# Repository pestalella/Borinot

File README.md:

# Borinot
Sensor de temperatura i humitat, que envia les dades que recull a una base de dades via WiFi

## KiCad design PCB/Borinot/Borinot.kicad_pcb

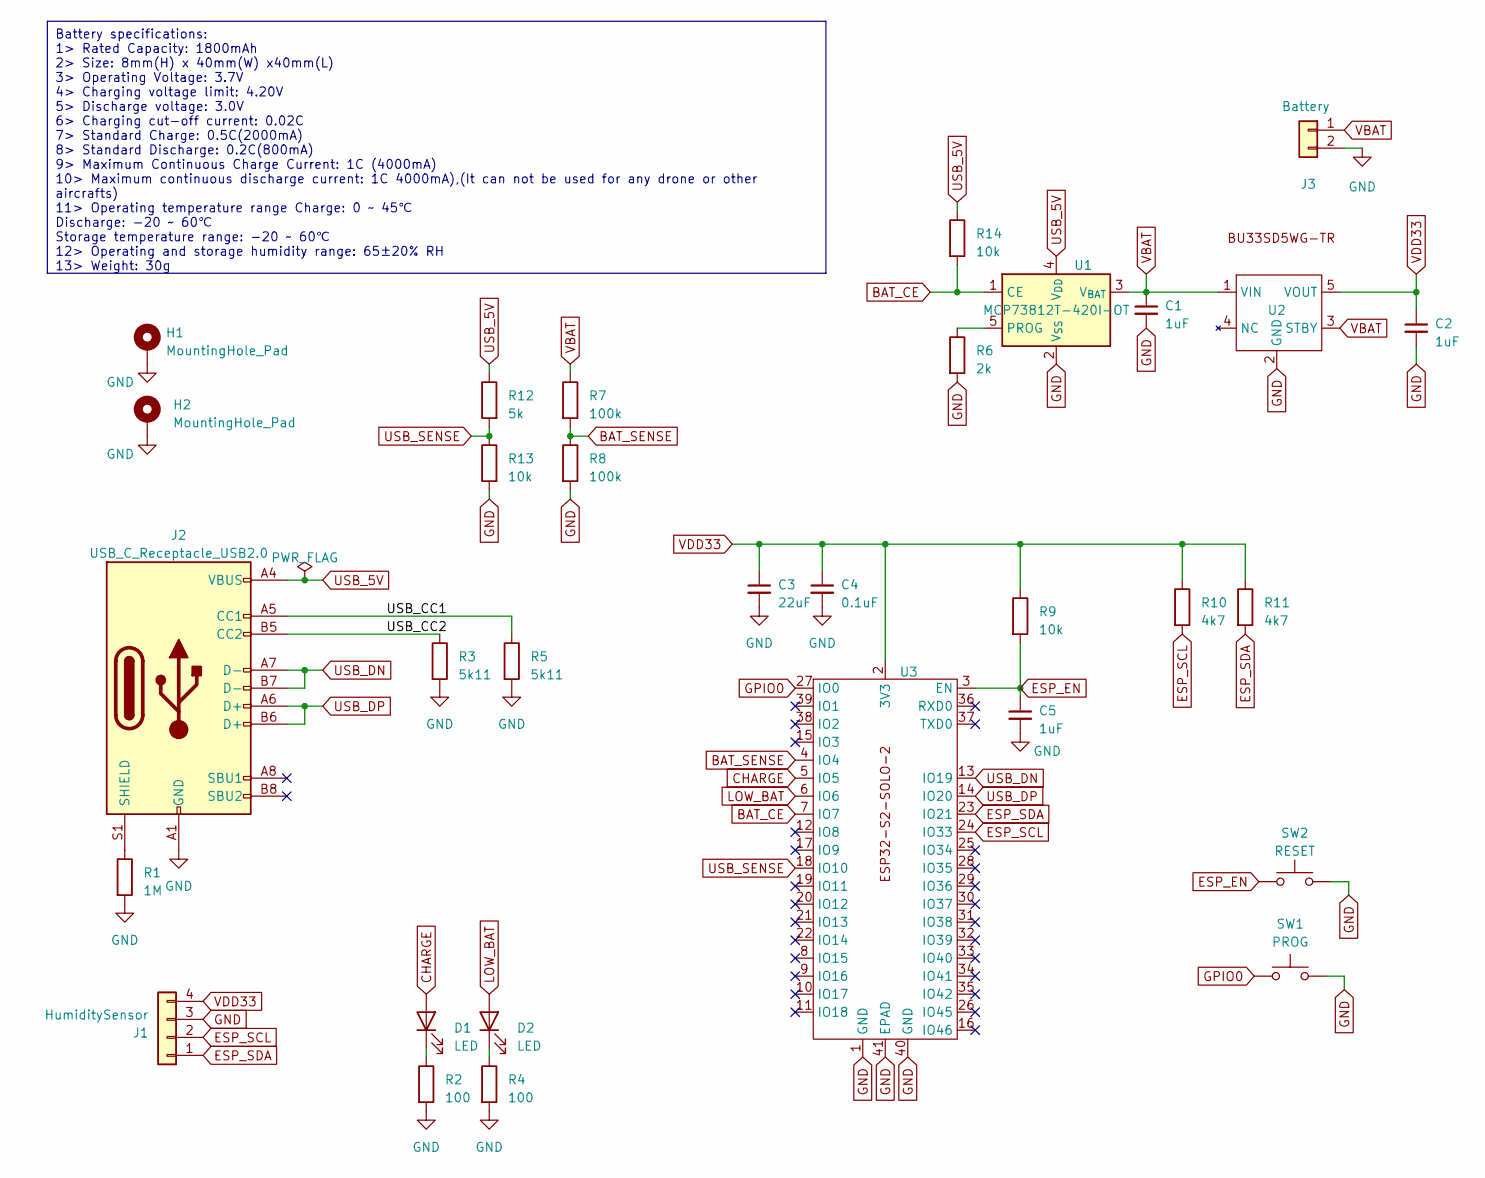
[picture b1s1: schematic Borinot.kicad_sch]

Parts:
C1, C2, C5: 1uF; C_0805_2012Metric_Pad1.18x1.45mm_HandSolder
C3: 22uF; C_0805_2012Metric_Pad1.18x1.45mm_HandSolder
C4: 0.1uF; C_0805_2012Metric_Pad1.18x1.45mm_HandSolder
D1, D2: LED; LED_0805_2012Metric
H1, H2: MountingHole_Pad; MountingHole_3.2mm_M3_Pad_Via
J1: HumiditySensor; Molex_KK-254_AE-6410-04A_1x04_P2.54mm_Vertical
J2: USB_C_Receptacle_USB2.0; USB_C_Receptacle_G-Switch_GT-USB-7010ASV
J3: Battery; PinHeader_1x02_P2.54mm_Vertical
R1: 1M; R_0805_2012Metric_Pad1.20x1.40mm_HandSolder
R2, R4: 100; R_0805_2012Metric_Pad1.20x1.40mm_HandSolder
R3, R5: 5k11; R_0805_2012Metric_Pad1.20x1.40mm_HandSolder
R6: 2k; R_0805_2012Metric_Pad1.20x1.40mm_HandSolder
R7, R8: 100k; R_0805_2012Metric_Pad1.20x1.40mm_HandSolder
R9, R13, R14: 10k; R_0805_2012Metric_Pad1.20x1.40mm_HandSolder
R10, R11: 4k7; R_0805_2012Metric_Pad1.20x1.40mm_HandSolder
R12: 5k; R_0805_2012Metric_Pad1.20x1.40mm_HandSolder
SW1: PROG; SW_PUSH_6mm
SW2: RESET; SW_PUSH_6mm
U1: MCP73812T-420I-OT; SOT-23-5
U2: SOT-23-5
U3: ESP32-S2-SOLO

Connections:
/USB_CC1: J2.A5 (CC1), R5.1
/USB_CC2: J2.B5 (CC2), R3.1
BAT_CE: R14.2, U1.1 (CE), U3.7 (IO7)
BAT_SENSE: R7.2, R8.1, U3.4 (IO4)
CHARGE: D1.2 (A), U3.5 (IO5)
ESP_EN: C5.1, R9.2, SW2.1, U3.3 (EN)
ESP_SCL: J1.2, R10.2, U3.24 (IO33)
ESP_SDA: J1.1, R11.2, U3.23 (IO21)
GND: C1.2, C2.2, C3.2, C4.2, C5.2, H1.1, H2.1, J1.3, J2.A1 (GND), J2.A12 (GND), J2.B1 (GND), J2.B12 (GND), J3.2, R1.2, R2.2, R3.2, R4.2, R5.2, R6.2, R8.2, R13.2, SW1.2, SW2.2, U1.2 (V_{SS}), U2.2 (GND), U3.1 (GND), U3.40 (GND), U3.41 (EPAD)
GPIO0: SW1.1, U3.27 (IO0)
LOW_BAT: D2.2 (A), U3.6 (IO6)
unnamed: D1.1 (K), R2.1
unnamed: D2.1 (K), R4.1
unnamed: J2.S1 (SHIELD), R1.1
unnamed: R6.1, U1.5 (PROG)
USB_5V: J2.A4 (VBUS), J2.A9 (VBUS), J2.B4 (VBUS), J2.B9 (VBUS), R12.1, R14.1, U1.4 (V_{DD})
USB_DN: J2.A7 (D-), J2.B7 (D-), U3.13 (IO19)
USB_DP: J2.A6 (D+), J2.B6 (D+), U3.14 (IO20)
USB_SENSE: R12.2, R13.1, U3.18 (IO10)
VBAT: C1.1, J3.1, R7.1, U1.3 (V_{BAT}), U2.1 (VIN), U2.3 (STBY)
VDD33: C2.1, C3.1, C4.1, J1.4, R9.1, R10.1, R11.1, U2.5 (VOUT), U3.2 (3V3)

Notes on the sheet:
Battery specifications: 1> Rated Capacity: 1800mAh 2> Size: 8mm(H) x 40mm(W) x40mm(L) 3> Operating Voltage: 3.7V 4> Charging voltage limit: 4.20V 5> Discharge voltage: 3.0V 6> Charging cut-off current: 0.02C 7> Standard Charge: 0.5C(2000mA) 8> Standard Discharge: 0.2C(800mA) 9> Maximum Continuous C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

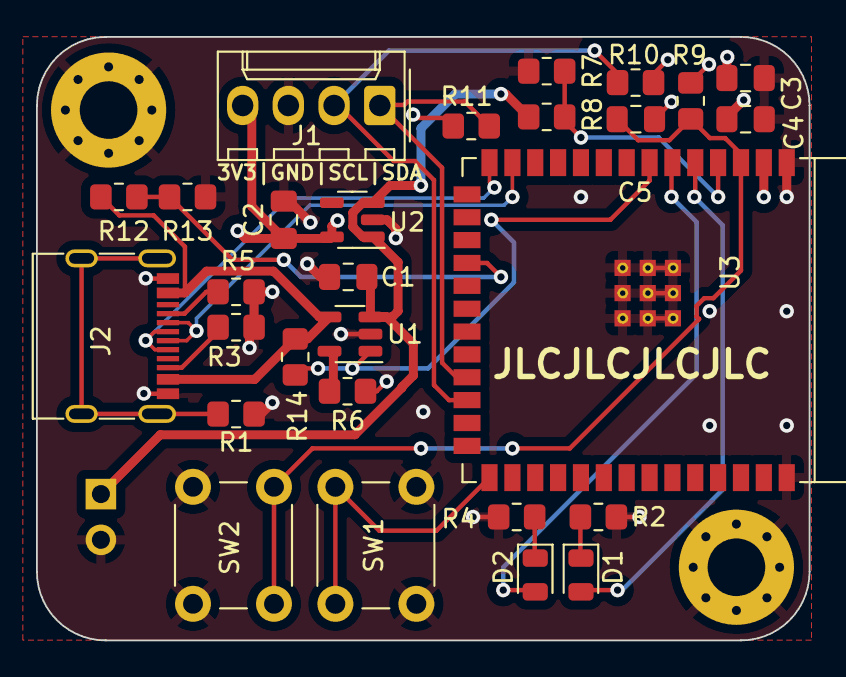
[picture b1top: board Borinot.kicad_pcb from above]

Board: 4 copper layers, 42.9 x 33.5 mm, 31 parts (1 on the bottom side), 21 nets.

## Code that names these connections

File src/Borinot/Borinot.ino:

#include "passwords.h"

#include "Adafruit_Sensor.h"
#include "Adafruit_AM2320.h"
#include "driver/adc.h"
#include "esp_adc_cal.h"
#include "esp_mac.h"
#include <Wire.h>

#include <WiFiMulti.h>
WiFiMulti wifiMulti;
#define DEVICE "ESP32"
#include <InfluxDbClient.h>
#include <InfluxDbCloud.h>

const char *ssid = WIFI_SSID;
const char *password = WIFI_PASSWORD;

// Time zone info
#define TZ_INFO "UTC2"

TwoWire I2CAM2320 = TwoWire(0);
Adafruit_AM2320 am2320 = Adafruit_AM2320(&I2CAM2320);

const int CHARGING_PIN = GPIO_NUM_5;
const int LOW_BAT_PIN = GPIO_NUM_6;
const int USB_SENSE = GPIO_NUM_10;

const int BAT_CHARGE_ENABLE = GPIO_NUM_7;

const int BATTERY_VOLTAGE_START_CHARGE = 3500;
const int BATTERY_VOLTAGE_STOP_CHARGE = 4150;

int batteryPoweredDelay = 10000; // 10 second delay
int millisecondsBetweenPosts = 600000;
int accumDelayBeforeSending = 0;

// Declare InfluxDB client instance with preconfigured InfluxCloud certificate
InfluxDBClient client(INFLUXDB_URL, INFLUXDB_ORG, INFLUXDB_BUCKET, INFLUXDB_TOKEN, InfluxDbCloud2CACert);

// Declare Data point
Point sensor("air_quality");

String h2S(uint8_t num)
{
	return (num < 16 ? "0" : "") + String(num, HEX);
}

void setup()
{
	Serial.begin(115200);
	pinMode(CHARGING_PIN, OUTPUT); // Indicator LED
	pinMode(LOW_BAT_PIN, OUTPUT);	 // Indicator LED
	pinMode(CHARGING_PIN, OUTPUT); // Indicator LED

	pinMode(USB_SENSE, INPUT_PULLDOWN); // USB sense pin (connected to USB 5V)
	pinMode(BAT_CHARGE_ENABLE, OUTPUT); // Battery charge enable pin

	delay(10);
	digitalWrite(BAT_CHARGE_ENABLE, 0); // Disable charging when starting

	if (!I2CAM2320.begin(21, 33))
	{
		Serial.println("Couldn't initialize I2C");
	}
	else
	{
		// unsigned status = bme.begin(0x77, &I2CAM2320);
		bool status = am2320.begin();

		if (!status)
		{
			Serial.println("Could not find a valid AM320 sensor, check wiring");
		}
	}

	// Setup wifi
	WiFi.mode(WIFI_STA);
	wifiMulti.addAP(ssid, password);

	Serial.print("Connecting to wifi");
	while (wifiMulti.run() != WL_CONNECTED)
	{
		Serial.print(".");
		delay(100);
	}
	Serial.println();

	// Accurate time is necessary for certificate validation and writing in batches
	// We use the NTP servers in your area as provided by: https://www.pool.ntp.org/zone/
	// Syncing progress and the time will be printed to Serial.
	timeSync(TZ_INFO, "pool.ntp.org", "time.nis.gov");

	// Check server connection
	if (client.validateConnection())
	{
		Serial.print("Connected to InfluxDB: ");
		Serial.println(client.getServerUrl());
	}
	else
	{
		Serial.print("InfluxDB connection failed: ");
		Serial.println(client.getLastErrorMessage());
	}

	uint8_t macAddress[10];
	if (esp_efuse_mac_get_default(macAddress) == ESP_OK)
	{

		String myID = "";
		for (int i = 5; i >= 0; i--)
			myID += h2S(macAddress[i]);
		sensor.addTag("SensorID", myID);
	}
	else
	{
		Serial.print("Couldn't read MAC address");
		sensor.addTag("SensorID", "UNKNOWN");
	}
	// Add tags to the data point
	sensor.addTag("device", DEVICE);
	sensor.addTag("SSID", WiFi.SSID());

	adc1_config_width(ADC_WIDTH_BIT_13);
	adc1_config_channel_atten(ADC1_CHANNEL_3, ADC_ATTEN_DB_11);
}

void loop()
{
	// Clear fields for reusing the point. Tags will remain the same as set above.
	sensor.clearFields();

	// Store measured value into point
	float temp = am2320.readTemperature();
	delay(200);
	float humidity = am2320.readHumidity();
	Serial.print("Temp: ");
	Serial.print(temp);
	Serial.print(" C  Humidity:");
	Serial.println(humidity);

	sensor.addField("Temp", temp);
	sensor.addField("RH", humidity);

	uint32_t analogReading = adc1_get_raw(ADC1_CHANNEL_3);
	uint32_t voltageRead = analogReading * 2500 / 8191 * 3730 / 3554;
	uint32_t batVoltage = voltageRead * 2;
	Serial.print("Raw value: " + String(analogReading));
	Serial.print(" bat voltage: ");
	Serial.print(batVoltage);
	Serial.println(" mV");
	sensor.addField("BAT_MILLIVOLTS", batVoltage);

	int canEnableCharge = (batVoltage < BATTERY_VOLTAGE_STOP_CHARGE) ? HIGH : LOW;
	int low_battery = (batVoltage <= BATTERY_VOLTAGE_START_CHARGE)? HIGH:LOW;
	int usb_connected = digitalRead(USB_SENSE);
	int charging = (usb_connected == HIGH) && (canEnableCharge == HIGH) ? HIGH:LOW;

	sensor.addField("USB_CONNECTED", usb_connected == HIGH);
	sensor.addField("LOW_BAT_VOLTAGE", low_battery == HIGH);
	sensor.addField("CHARGING", charging == HIGH);

	digitalWrite(CHARGING_PIN, charging);
	digitalWrite(BAT_CHARGE_ENABLE, charging);
	digitalWrite(LOW_BAT_PIN, low_battery);

	// Check WiFi connection and reconnect if needed
	if (wifiMulti.run() != WL_CONNECTED)
	{
		Serial.println("Wifi connection lost");
	}

	if (usb_connected) {
		uint8_t macAddress[10];
		if (esp_efuse_mac_get_default(macAddress) == ESP_OK)
		{

			String myID = "";
			for (int i = 5; i >= 0; i--)
				myID += h2S(macAddress[i]);
			Serial.println("ID:" + myID);
		}

		if (accumDelayBeforeSending >= millisecondsBetweenPosts) {
			// Write point
			Serial.print("Writing: ");
			Serial.println(sensor.toLineProtocol());
			if (!client.writePoint(sensor))
			{
				Serial.print("InfluxDB write failed: ");
				Serial.println(client.getLastErrorMessage());
			}
			accumDelayBeforeSending = 0;
		} else {
			accumDelayBeforeSending += batteryPoweredDelay;
		}
		delay(batteryPoweredDelay);
	} else {
		if (!client.writePoint(sensor))
		{
			Serial.print("InfluxDB write failed: ");
			Serial.println(client.getLastErrorMessage());
		}
		// Running on battery, deep sleep is needed.
		esp_sleep_enable_timer_wakeup(millisecondsBetweenPosts * 1000ULL);
		esp_deep_sleep_start();
	}
}

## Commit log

2023-03-08 Initial import of PCB design
    Add Kicad PCB design files for the initial version
    of the PCB.
2023-03-08 Add project box design files
    Initial sketches of the pcb in FreeCAD to design a box to
    fit the pcb and the battery.
2023-03-10 Start constructing the box
2023-03-15 Finished project box
    First version of the project box, now ready to be printed.
2023-04-26 Four-layer board
    Moved the design to a four-layer board, to simplify routing.
2023-04-26 Add .gitignore file
2023-05-02 Battery management change
    Use an easier-to-solder SOT-23-5-packaged battery manager
    to simplify the soldeering of the PCBs.
2023-05-24 Initial import of firmware code
2023-05-24 Remove v2 commented-out code
    The v2 code is not needed in this branch.
2023-05-25 Recover firmware for PCBs v0.2
2023-05-26 Add missing pull-up on ChargeEnable pin
    Without a pull-up to USB 5V on that pin it is impossible
    to start the ESP32 when the battery is below 3.3V
    Added a voltage divider to sense the 5V from USB and
    be able to decide whether to charge the battery or not.
2023-05-30 Add support for USB sensing
    Sense the 5V from USB, and be more responsive when powered
    by USB by not going to deep sleep.
    Add this info to the data sent to InfluxDB.
2023-07-17 Add new .gitignores
2023-07-17 Show ID over serial at boot
